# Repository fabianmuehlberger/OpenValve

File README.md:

# OpenValve
open source smarthome radiator thermostat

This project has the goal of developing an open source smarthome valve for radiators. 

## IDEA
* Using “off the shelf” components and 3D printed parts for easy building 
* keep  the cost at a minimum 
* allow programming via common environments (ESP-IDF, ESPHome) 
* integration into smarthome with ESPHome and Home Assistant

##  COMPONENTS
* Linear Stepper Motor for smart radiator valve
* 3D printed parts
* PCB 
  * ESP32 based board (esp32-c6 or esp32-c3)
  * stepper driver TMC 2300 
  * Battery management/ voltage regulator

## Mechanical design
The general idea is to make the mechanical Assembly and the program as simple as possible, to make it accessible and easy to work with. This is the premise for all design decisions   

### Radiator Valve 

(standard radiator valve, used in Austria)
this sort of valve has a pin with ~2.5mmm travel, this allows for a controlled liquid flow depending on the distance. 
To make the SmartValve adjustable, a mechanism is needed to control the pin in that region. 

### Motor / Drive
The current development uses a geared stepper motor with 10:1 ration and a linear travel of ~ 5mm. The stepper is designed for this application.

### 3D printed parts
OpenValve is designed to have 3d printed parts that are printable with a standard FTM printer with no supports and assembled with m3 bolts and buts.    

[OnShape](https://cad.onshape.com/documents/391453e964c4cf36b71477fb/w/96218fe9ab75c37b541d1e8c/e/7027b69015998d7833889829?renderMode=0&uiState=64fb2ffe75317b0599136144https://cad.onshape.com/documents/391453e964c4cf36b71477fb/w/96218fe9ab75c37b541d1e8c/e/7027b69015998d7833889829?renderMode=0&uiState=64fb2ffe75317b0599136144) is used for the projecrt for easy collaboration and versioning.

## SOFTWARE
* For easy integration in Home Assistant, the project is written in Arduino framework, this makes it possible to compile it as a ESPHome device

## TODO

### Prove of concept
- [x] 3D printed parts 
- [x] Arduino test sketch

### Prototype
- [ ] PCB design
  - [x] Schematic design
  - [x] Part selection for PCB
  - [x] PCB layout and Design
  - [x] PCB ordered
- [x] Prototype built
- [ ] Prototype tested
- [ ] prototype documentation

### Beta
- [ ] ESPHome code
- [ ] Home Assistant integration
- [ ] Durability test
- [ ] Beta documentation
- [ ] power consumption test

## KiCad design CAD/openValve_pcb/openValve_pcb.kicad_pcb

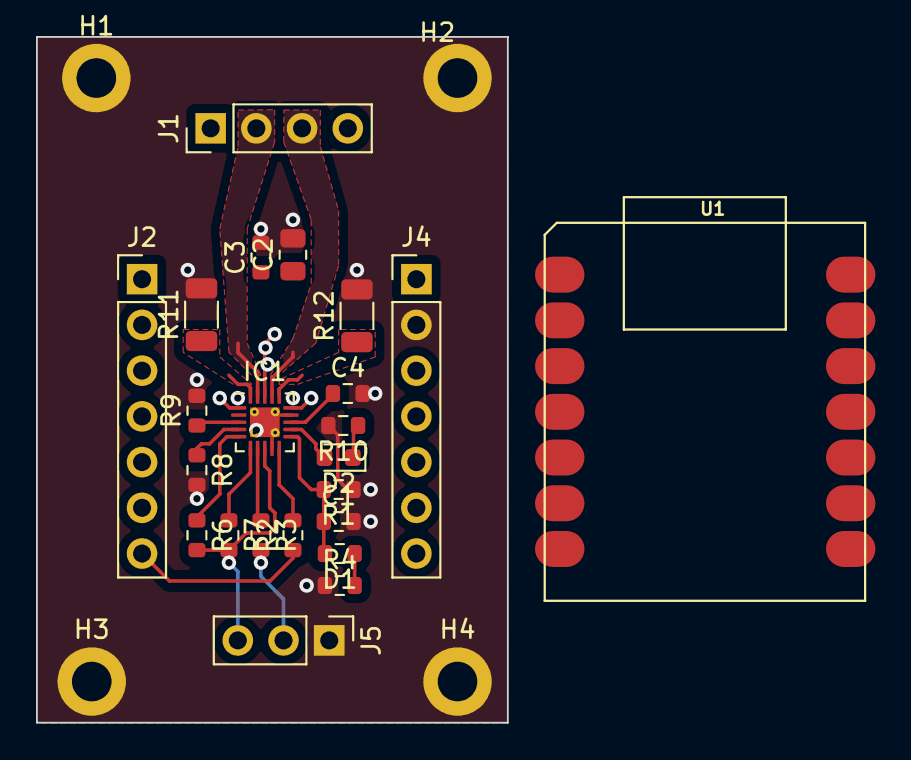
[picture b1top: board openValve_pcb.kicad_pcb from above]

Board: 2 copper layers, 26.2 x 38.1 mm, 27 parts (0 on the bottom side), 22 nets.

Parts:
C1, C3, C4: 100n; R_0603_1608Metric
C2: 10u; R_0805_2012Metric
D1: 0603/LED; R_0603_1608Metric
D2: white/0603; LED_0603_1608Metric
H1, H2, H3, H4: MountingHole_Pad; MountingHole_2.2mm_M2_DIN965_Pad
IC1: TMC2300; QFN-20-1EP_3x3mm_P0.4mm_EP1.65x1.65mm_ThermalVias
J1: Conn_01x04_Pin; PinHeader_1x04_P2.54mm_Vertical
J2: Conn_01x07_Pin; PinHeader_1x07_P2.54mm_Vertical
J4: Conn_01x08_Pin; PinHeader_1x07_P2.54mm_Vertical
J5: Conn_01x03_Pin; PinHeader_1x03_P2.54mm_Vertical
R1, R2, R3, R6, R7, R8, R9: 100k; R_0603_1608Metric
R4, R10: 1k; R_0603_1608Metric
R11, R12: 220; R_1206_3216Metric
U1: MOUDLE-SEEEDUINO-XIAO-ESP32C3; MOUDLE14P-SMD-2.54-21X17.8MM

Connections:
+3.3V: C2.1, C3.1, IC1.8 (STEPPER), IC1.18 (VS), J4.3, J5.3, R6.2, R7.2, U1.12 (3V3)
+5V: J4.1, U1.14 (5V)
/DIAG: D2.2 (A), IC1.12 (DIAG), J2.2, U1.2 (PA4_A1_D1)
/DIR: IC1.3 (DIR), J2.4, R9.1, U1.4 (PA11_A3_D3)
/EN: IC1.7 (EN), J2.6, R3.1, U1.6 (PA9_A5_D5_SCL)
/MS1\AD0: IC1.5 (MS1/AD0), R6.1
/MS2\AD1: IC1.6 (MS2/AD1), R7.1
/OA1: IC1.19 (OA1), J1.2
/OA2: IC1.1 (OA2), J1.1
/OB1: IC1.17 (OB1), J1.3
/OB2: IC1.15 (OB2), J1.4
/PD/UART: IC1.10 (e~PD/UART), J4.7, R2.2, U1.8 (PB09_A7_D7_RX)
/SENS A: IC1.20 (BRA), R11.1
/SENS B: IC1.16 (BRB), R12.1
/STDBY: C1.1, D1.2 (A), IC1.11 (VIO/~STDBY), J2.3, R1.2, U1.3 (PA10_A2_D2)
/STEP: IC1.4 (STEP), J2.5, R8.1, U1.5 (PA8_A4_D4_SDA)
/TX: J2.7, R2.1, U1.7 (PB08_A6_D6_TX)
GND: C1.2, C2.2, C3.2, C4.2, H1.1, H2.1, H3.1, H4.1, IC1.9 (MODE), IC1.14 (GND), IC1.21 (PAD), J4.2, J5.1, R1.1, R4.1, R8.2, R9.2, R10.2, R11.2, R12.2, U1.13 (GND)
unnamed: D1.1 (K), R4.2
unnamed: D2.1 (K), R10.1
unnamed: C4.1, IC1.13 (1,8Vout)
unnamed: J5.2, R3.2

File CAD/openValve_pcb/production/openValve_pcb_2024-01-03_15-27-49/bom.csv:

Designator,Footprint,Quantity,Value,LCSC Part #
"C1, C3, C4",0603,3,100n,
C2,0805,1,10u,
D1,0603,1,0603/LED,
D2,0603,1,white/0603,
"H1, H2, H3, H4",MountingHole_2.2mm_M2_DIN965_Pad,4,MountingHole_Pad,
IC1,QFN-20-1EP_3x3mm_P0.4mm_EP1.65x1.65mm_ThermalVias,1,TMC2300,
J1,PinHeader_1x04_P2.54mm_Vertical,1,Conn_01x04_Pin,
J2,PinHeader_1x07_P2.54mm_Vertical,1,Conn_01x07_Pin,
J4,PinHeader_1x07_P2.54mm_Vertical,1,Conn_01x08_Pin,
J5,PinHeader_1x03_P2.54mm_Vertical,1,Conn_01x03_Pin,
"R1, R2, R3, R6, R7, R8, R9",0603,7,100k,
"R10, R4",0603,2,1k,
"R11, R12",1206,2,220,
U1,MOUDLE14P-SMD-2.54-21X17.8MM,1,MOUDLE-SEEEDUINO-XIAO-ESP32C3,

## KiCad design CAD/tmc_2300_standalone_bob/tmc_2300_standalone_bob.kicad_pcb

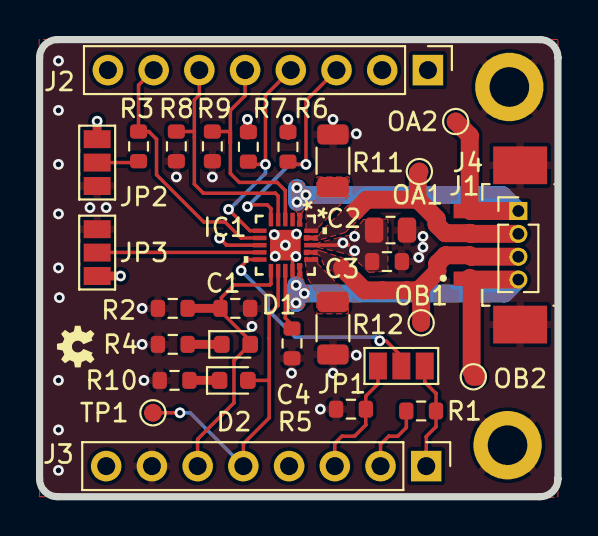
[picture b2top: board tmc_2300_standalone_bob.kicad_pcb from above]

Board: 4 copper layers, 28.8 x 25.4 mm, 33 parts (0 on the bottom side), 24 nets.

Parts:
C1, C3, C4: 100n; R_0603_1608Metric
C2: 10u; R_0805_2012Metric
D1, D2: LED; LED_0603_1608Metric
H1, H2: MountingHole_Pad; MountingHole_2.2mm_M2_DIN965_Pad
IC1: TMC2300; QFN20_3x3_TRI
J1: Conn_01x04_Pin; PinHeader_1x04_P1.27mm_Vertical
J2, J3: Conn_01x08_Pin; PinHeader_1x08_P2.54mm_Vertical
J4: 53261-0471; MOLEX_53261-0471
JP1, JP2, JP3: SolderJumper_3_Open; SolderJumper-3_P1.3mm_Open_Pad1.0x1.5mm_NumberLabels
R1, R2, R3, R4, R5, R6, R7, R8, R9: 100k; R_0603_1608Metric
R10: 220; R_0603_1608Metric
R11, R12: 220; R_1206_3216Metric
TP1, TP4, TP5, TP6, TP7: TestPoint; TestPoint_Pad_D1.0mm

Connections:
+3.3V: C2.1, C3.1, IC1.8 (STEPPER), IC1.18 (VS), J2.8, JP2.1 (A), JP3.3 (B), R6.2, R7.2
/DIAG: D2.2 (A), IC1.12 (DIAG), J3.5, TP1.1
/DIR: IC1.3 (DIR), J2.5, R9.1
/EN: IC1.7 (EN), J2.7, R3.1
/MODE: IC1.9 (MODE), JP3.2 (C)
/MS1\AD0: IC1.5 (MS1/AD0), J2.3, R6.1
/MS2\AD1: IC1.6 (MS2/AD1), J2.4, R7.1
/OA1: IC1.19 (OA1), J1.2, J4.3, TP4.1
/OA2: IC1.1 (OA2), J1.1, J4.4, TP5.1
/OB1: IC1.17 (OB1), J1.3, J4.2, TP6.1
/OB2: IC1.15 (OB2), J1.4, J4.1, TP7.1
/PD: J3.3, JP1.1 (A), R5.2
/PD/UART: IC1.10 (e~PD/UART), JP1.2 (C)
/RX: J3.1, JP1.3 (B), R1.2
/SENS A: IC1.20 (BRA), R11.1
/SENS B: IC1.16 (BRB), R12.1
/STDBY: C1.1, D1.2 (A), IC1.11 (VIO/~STDBY), J3.6, R2.2
/STEP: IC1.4 (STEP), J2.6, R8.1
/TX: J3.2, R1.1
GND: C1.2, C2.2, C3.2, C4.2, H1.1, H2.1, IC1.14 (GND), IC1.21 (PAD), J3.7, J4.SH1 (SHIELD), J4.SH2 (SHIELD), JP2.3 (B), JP3.1 (A), R2.1, R4.1, R5.1, R8.2, R9.2, R10.2, R11.2, R12.2
unnamed: D1.1 (K), R4.2
unnamed: D2.1 (K), R10.1
unnamed: C4.1, IC1.13 (1,8Vout)
unnamed: JP2.2 (C), R3.2

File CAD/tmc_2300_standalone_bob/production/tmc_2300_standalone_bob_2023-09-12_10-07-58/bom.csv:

Designator,Footprint,Quantity,Value,LCSC Part #
"C1, C3, C4",0603,3,100n,
C2,0805,1,10u,
D1,0603,1,0603/LED,
D2,0603,1,white/0603,
IC1,QFN20_3x3_TRI,1,TMC2300,
"J2, J3",PinHeader_1x08_P2.54mm_Vertical,2,Conn_01x08_Pin,
"R1, R2, R3, R4, R5, R6, R7",0603,7,100k,
"R10, R9",1206,2,220,
R8,0603,1,220,

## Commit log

2022-09-07 added project outline
2023-07-26 Update README.md
    proof of cocept mechanical design
2023-07-26 Add files via upload
    upload of 3D model
2023-07-26 first simple sketch to for testing purposes.
2023-07-26 Update README.md
    corrected pictures
2023-07-29 updated code, added photo of prototype
2023-07-30 added notes
2023-09-08 changed pictures
2023-09-08 changed to prototype version 2
2023-09-08 added Photos
2023-09-08 added gitignore, removed old step files
2023-09-12 tmc2300 bob
    added custom bob for the tmc2300 driver to fit the lilygo t-oi MCU
2023-09-12 Update README.md
    updated todo
2023-09-13 fixed schematic
2023-09-15 Update README.md
    changed title
2023-10-17 removed old main.ino, changed gitignore
2023-10-18 changed wrong resistor values in schematic
2023-10-23 updated components
2023-12-01 updated pictures
2023-12-01 update of included pictures
2024-01-03 created xiao compatible board
